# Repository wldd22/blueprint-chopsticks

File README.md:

# Chopsticks
A board with a screen and capacitive pads to play the common hand game, chopsticks, with a perfect algorithm! Originally made for [Hackclub's Blueprint](https://blueprint.hackclub.com/)

## Details
PCB made using KiCAD \
Firmware made with CircuitPython

## About
There was no 3D modelling involved in this project, because I wanted the final outcome to be as minimal as possible. Just a flat PCB with a chip and a screen. I wanted to make a chopsticks AI for a few months, and after making the code for it, I wanted to make a piece of hardware that you could play it with.

## Images

### Schematic

### PCB

## BOM
| Item | Description | Quantity | Source | Cost | Amount |
| --- | --- | --- | --- | --- | --- |
| Seeed Studio XIAO RP2040 | Microcontroller | 1 | [Robu](https://robu.in/product/seeed-studio-xiao-rp2040-v1-0/) | ₹529.00 | ₹529.00 |
| SSD1306 I2C OLED Display | 128x32 OLED | 1 | [Robu](https://robu.in/product/0-91-inch-128x32-i2c-iic-serial-blue-oled-lcd-display-module/) | ₹212.00 | ₹212.00 |
| Robu Shipping | Standard Shipping | - | - | - | ₹49.00 |
| **TOTAL** | | | | | ₹790.00 ≈ USD$8.20 |

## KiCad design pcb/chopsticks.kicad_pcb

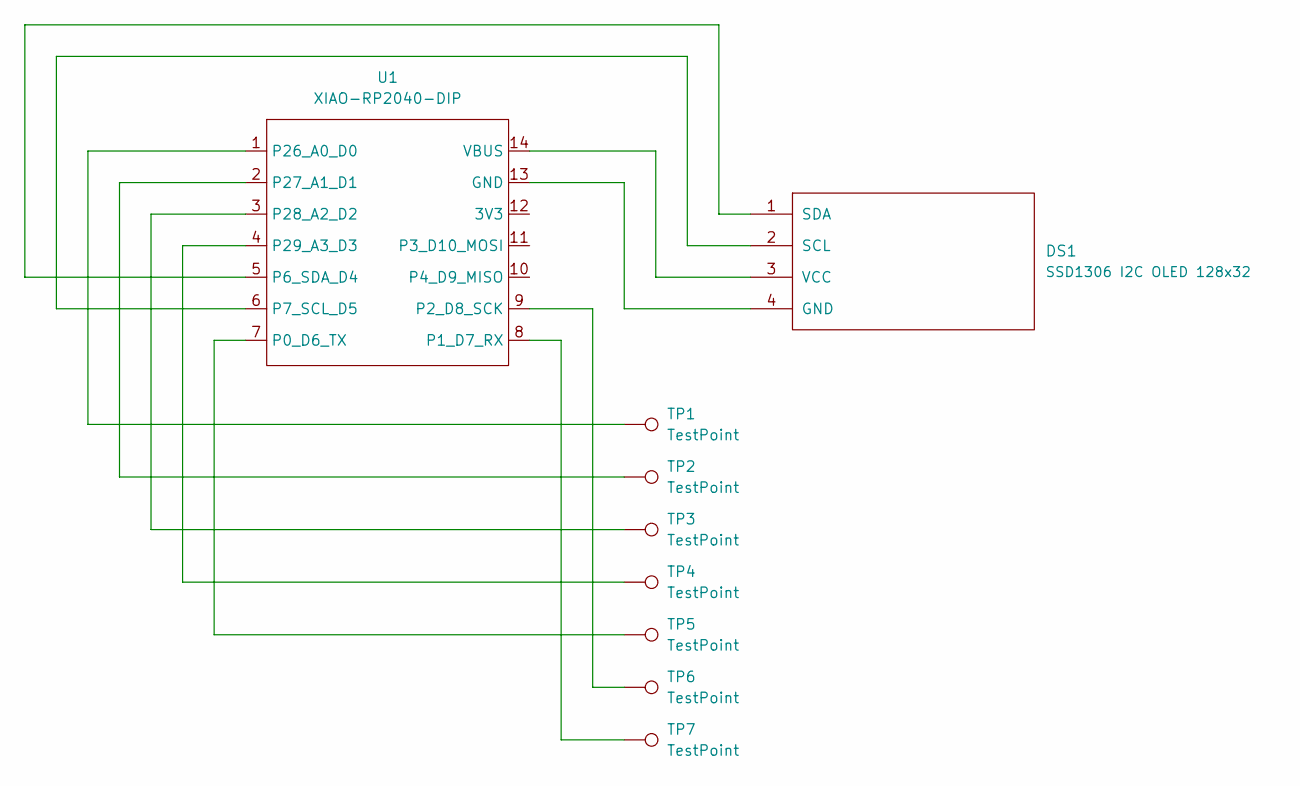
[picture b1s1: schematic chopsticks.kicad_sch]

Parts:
DS1: SSD1306 I2C OLED 128x32
TP1, TP2, TP3, TP4: TestPoint; CAP_CIRCLE_PAD
TP5, TP6, TP7: TestPoint; CAP_RECT_PAD
U1: XIAO-RP2040-DIP

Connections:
unnamed: DS1.4 (GND), U1.13 (GND)
unnamed: DS1.2 (SCL), U1.6 (P7_SCL_D5)
unnamed: DS1.1 (SDA), U1.5 (P6_SDA_D4)
unnamed: DS1.3 (VCC), U1.14 (VBUS)
unnamed: TP5.1, U1.7 (P0_D6_TX)
unnamed: TP7.1, U1.8 (P1_D7_RX)
unnamed: TP6.1, U1.9 (P2_D8_SCK)
unnamed: TP1.1, U1.1 (P26_A0_D0)
unnamed: TP2.1, U1.2 (P27_A1_D1)
unnamed: TP3.1, U1.3 (P28_A2_D2)
unnamed: TP4.1, U1.4 (P29_A3_D3)

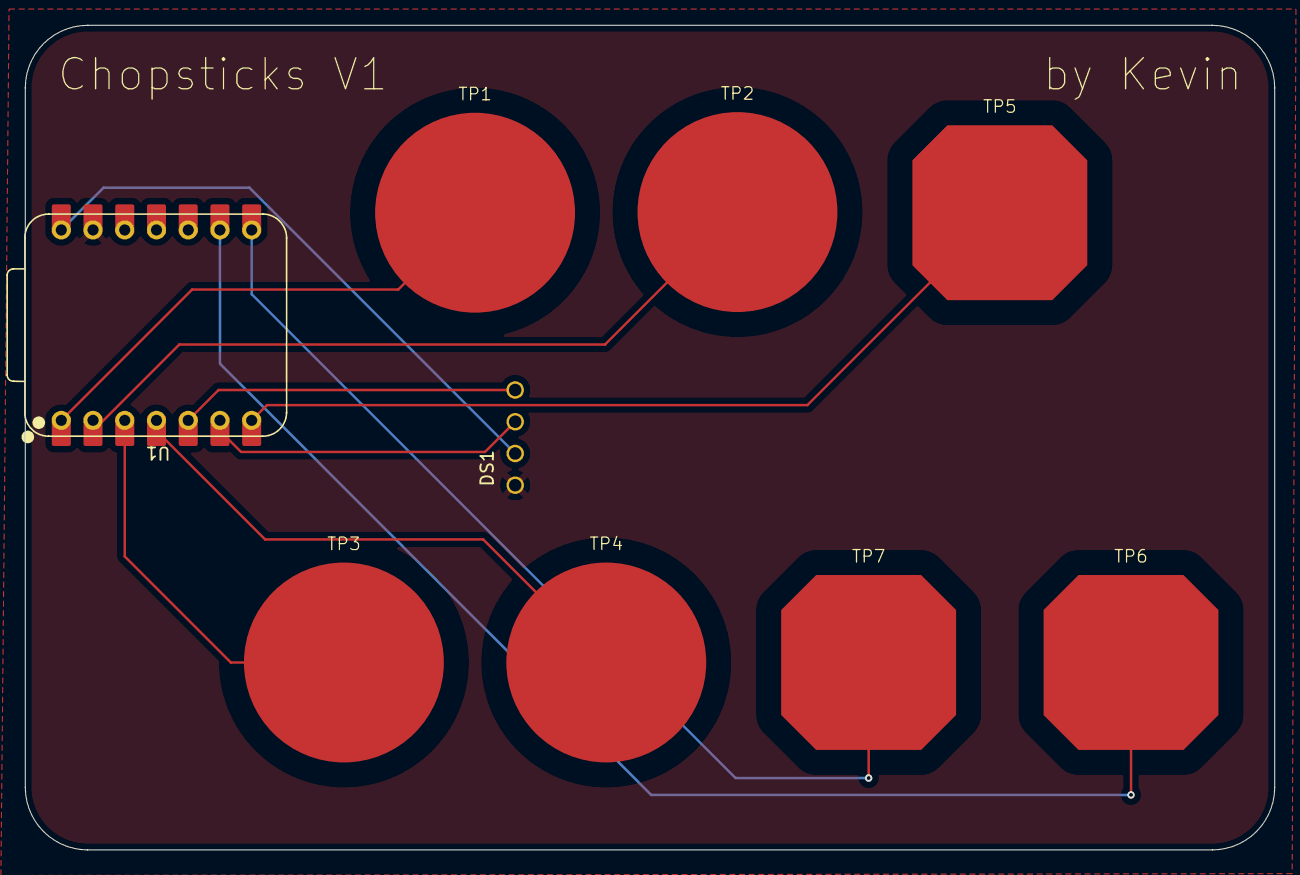
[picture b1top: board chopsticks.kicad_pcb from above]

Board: 2 copper layers, 100.0 x 66.0 mm, 9 parts (0 on the bottom side), 11 nets.

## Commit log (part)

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2026-03-27 Add PCB
2026-03-27 Add .gitignore
2026-03-27 Modify PCB
2026-03-27 Add /images
2026-03-29 Add gerber files
2026-03-29 Final ?
2026-03-29 Add CircuitPython firmware
2026-04-22 Added 3D CAD render
2026-04-22 Add CAD image
